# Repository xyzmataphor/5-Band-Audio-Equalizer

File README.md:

# 5-Band-Audio-Equalizer
This project presents the complete design and simulation of a 5-band analog graphic audio equalizer using the Active Inverting Bandpass Filter topology with LT1022 operational amplifiers in simulation and NE5532 for the physical PCB implementation. The equalizer is designed to independently control five frequency bands spanning the full audio range from 60 Hz to 16 kHz, making it suitable for music playback, recording, and general audio signal processing applications.

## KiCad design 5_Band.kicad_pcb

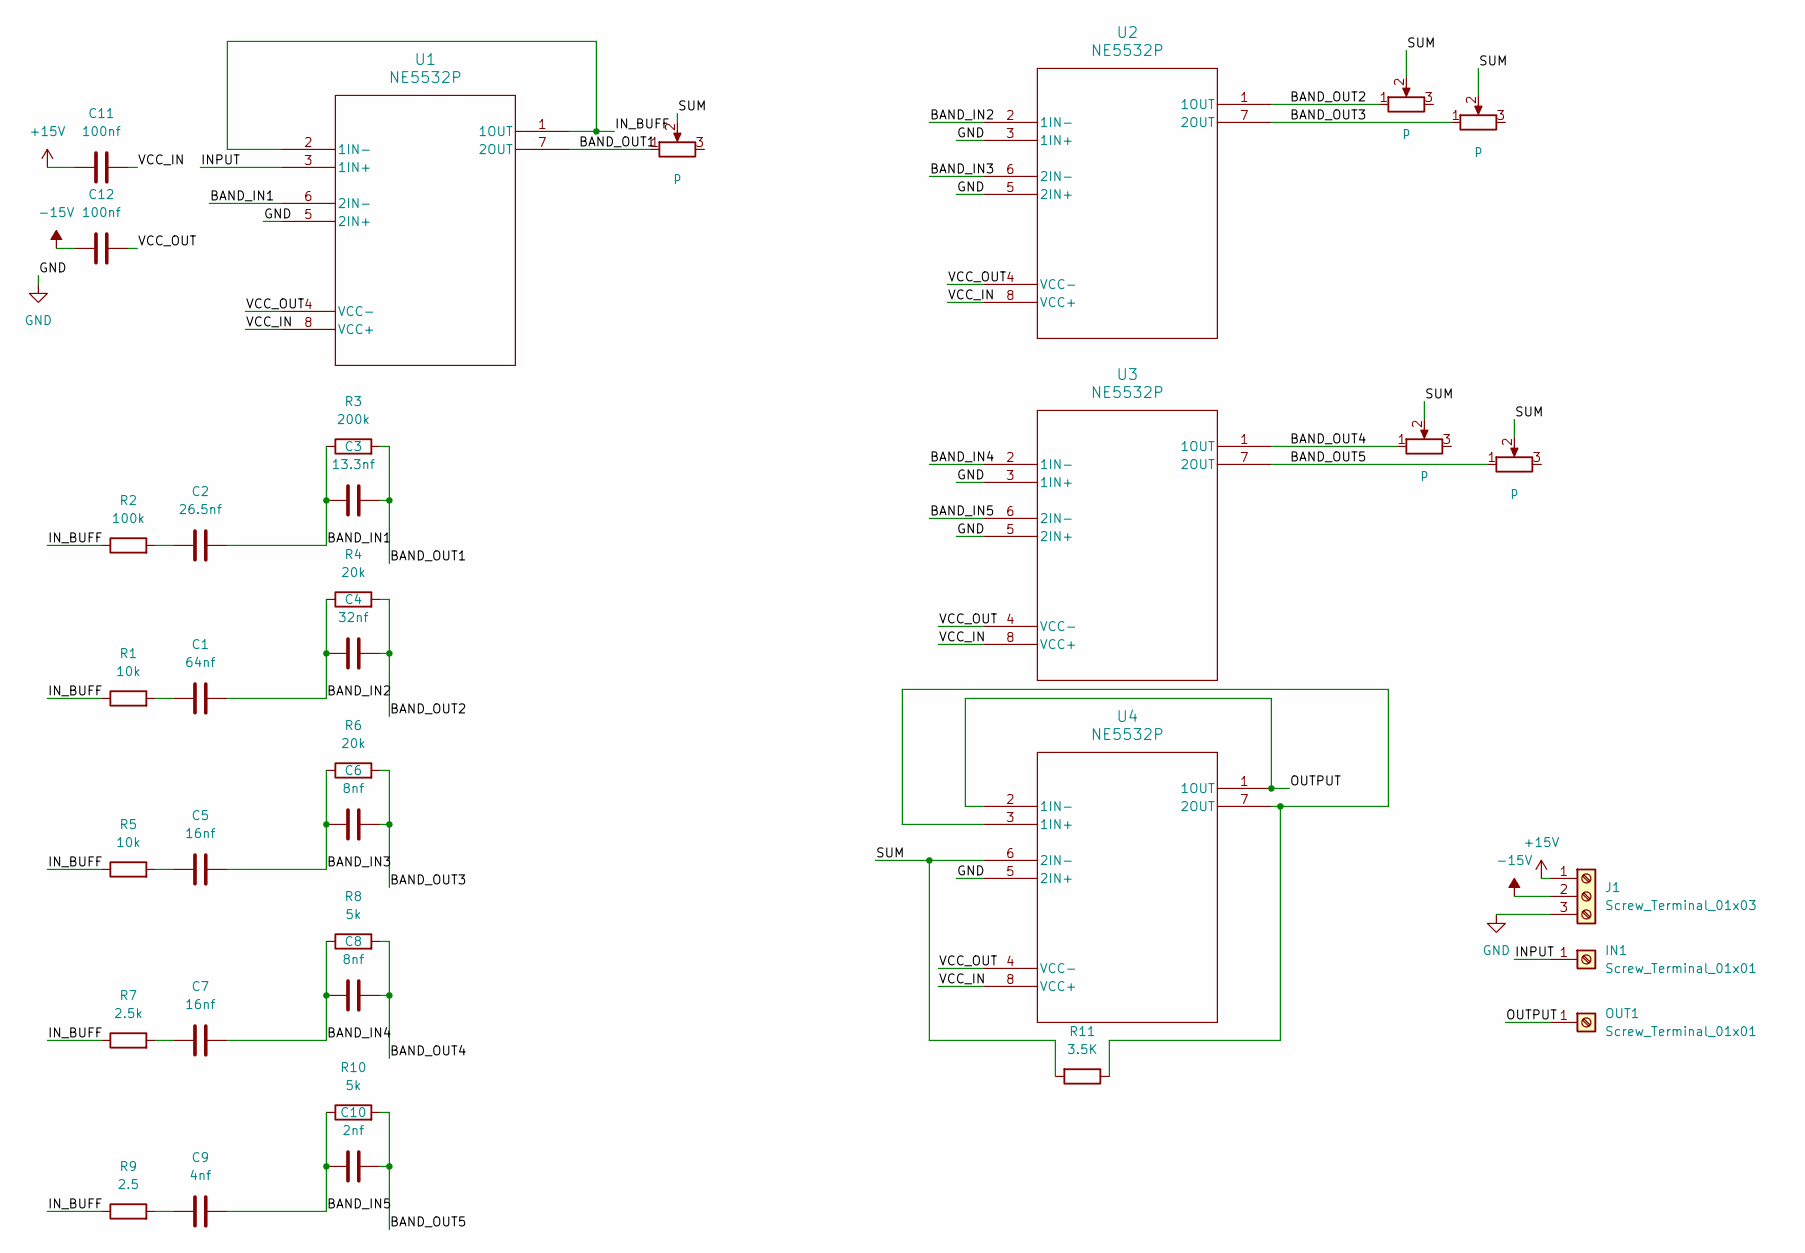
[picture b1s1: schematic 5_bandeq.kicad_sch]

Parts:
C1: 64nf; C_Disc_D5.0mm_W2.5mm_P5.00mm
C2: 26.5nf; C_Disc_D5.0mm_W2.5mm_P5.00mm
C3: 13.3nf; C_Disc_D5.0mm_W2.5mm_P5.00mm
C4: 32nf; C_Disc_D5.0mm_W2.5mm_P5.00mm
C5, C7: 16nf; C_Disc_D5.0mm_W2.5mm_P5.00mm
C6, C8: 8nf; C_Disc_D5.0mm_W2.5mm_P5.00mm
C9: 4nf; C_Disc_D5.0mm_W2.5mm_P5.00mm
C10: 2nf; C_Disc_D5.0mm_W2.5mm_P5.00mm
C11, C12: 100nf; C_Disc_D5.0mm_W2.5mm_P5.00mm
IN1: Screw_Terminal_01x01; PinHeader_1x01_P1.00mm_Horizontal
J1: Screw_Terminal_01x03; TerminalBlock_Phoenix_PT-1,5-3-5.0-H_1x03_P5.00mm_Horizontal
OUT1: Screw_Terminal_01x01; PinHeader_1x01_P1.00mm_Horizontal
R1, R5: 10k; R_Axial_DIN0207_L6.3mm_D2.5mm_P10.16mm_Horizontal
R2: 100k; R_Axial_DIN0207_L6.3mm_D2.5mm_P10.16mm_Horizontal
R3: 200k; R_Axial_DIN0207_L6.3mm_D2.5mm_P10.16mm_Horizontal
R4, R6: 20k; R_Axial_DIN0207_L6.3mm_D2.5mm_P10.16mm_Horizontal
R7: 2.5k; R_Axial_DIN0207_L6.3mm_D2.5mm_P10.16mm_Horizontal
R8, R10: 5k; R_Axial_DIN0207_L6.3mm_D2.5mm_P10.16mm_Horizontal
R9: 2.5; R_Axial_DIN0207_L6.3mm_D2.5mm_P10.16mm_Horizontal
R11: 3.5K; R_Axial_DIN0207_L6.3mm_D2.5mm_P10.16mm_Horizontal
RV1, RV2, RV3, RV4, RV5: p; Potentiometer_Bourns_PTV09A-1_Single_Vertical
U1, U2, U3, U4: NE5532P; P8

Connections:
+15V: C11.1, J1.1
-15V: C12.1, J1.2
/BAND_IN1: C2.2, C3.1, R3.1, U1.6 (2IN-)
/BAND_IN2: C1.2, C4.1, R4.1, U2.2 (1IN-)
/BAND_IN3: C5.2, C6.1, R6.1, U2.6 (2IN-)
/BAND_IN4: C7.2, C8.1, R8.1, U3.2 (1IN-)
/BAND_IN5: C9.2, C10.1, R10.1, U3.6 (2IN-)
/BAND_OUT1: C3.2, R3.2, RV1.1, U1.7 (2OUT)
/BAND_OUT2: C4.2, R4.2, RV2.1, U2.1 (1OUT)
/BAND_OUT3: C6.2, R6.2, RV3.1, U2.7 (2OUT)
/BAND_OUT4: C8.2, R8.2, RV4.1, U3.1 (1OUT)
/BAND_OUT5: C10.2, R10.2, RV5.1, U3.7 (2OUT)
/INPUT: IN1.1, U1.3 (1IN+)
/IN_BUFF: R1.1, R2.1, R5.1, R7.1, R9.1, U1.1 (1OUT), U1.2 (1IN-)
/OUTPUT: OUT1.1, U4.1 (1OUT), U4.2 (1IN-)
/SUM: R11.2, RV1.2, RV2.2, RV3.2, RV4.2, RV5.2, U4.6 (2IN-)
/VCC_IN: C11.2, U1.8 (VCC+), U2.8 (VCC+), U3.8 (VCC+), U4.8 (VCC+)
/VCC_OUT: C12.2, U1.4 (VCC-), U2.4 (VCC-), U3.4 (VCC-), U4.4 (VCC-)
GND: J1.3, U1.5 (2IN+), U2.3 (1IN+), U2.5 (2IN+), U3.3 (1IN+), U3.5 (2IN+), U4.5 (2IN+)
unnamed: C1.1, R1.2
unnamed: C2.1, R2.2
unnamed: C5.1, R5.2
unnamed: C7.1, R7.2
unnamed: C9.1, R9.2
unnamed: R11.1, U4.3 (1IN+), U4.7 (2OUT)

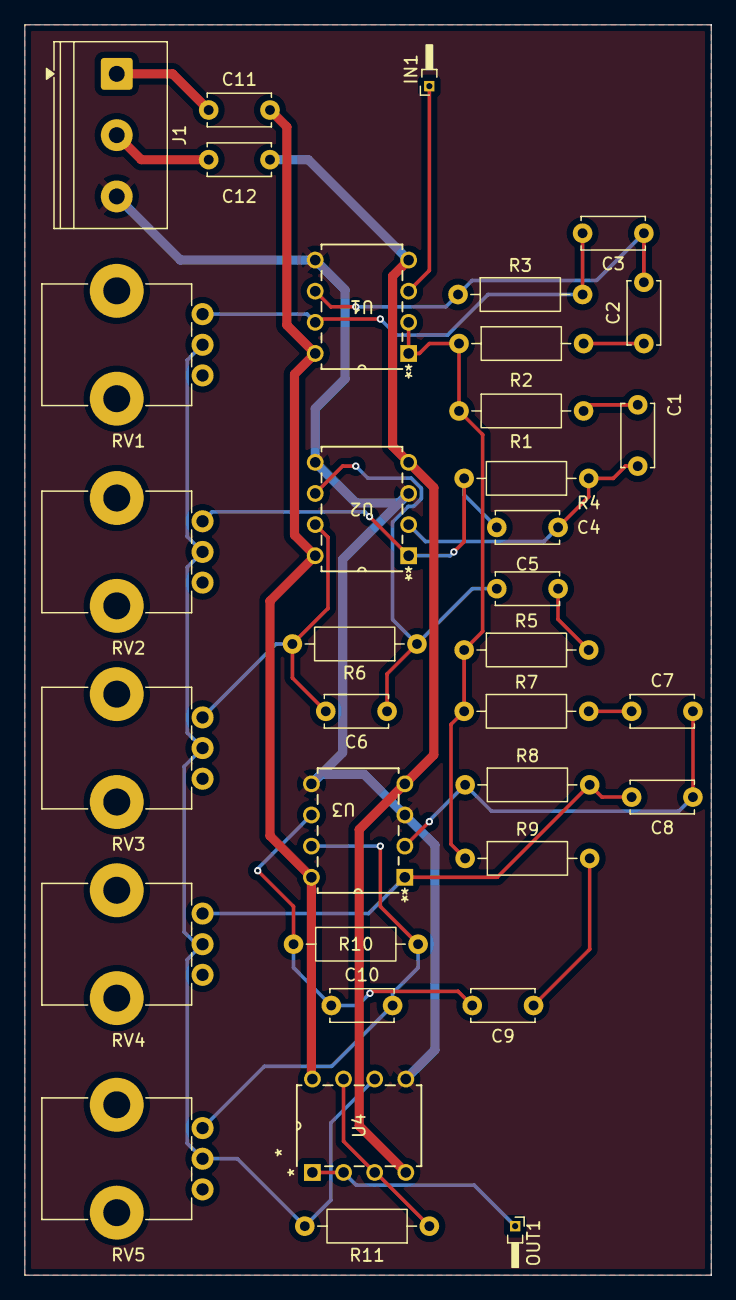
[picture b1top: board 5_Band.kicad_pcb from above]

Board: 2 copper layers, 56.0 x 102.0 mm, 35 parts (0 on the bottom side), 25 nets.

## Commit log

2026-06-10 Rename 5_BAND.asc to LTSPICE_Simulation.asc
2026-06-10 Rename 5_bandeq.kicad_pcb to 5_Band.kicad_pcb
2026-06-10 Rename LTSPICE_Simulation.asc to 5_Band_Simulation.asc
2026-06-10 Rename 5_bandeq.kicad_sch to 5_Band.kicad_sch
